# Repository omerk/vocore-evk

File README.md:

# vocore-evk

An evaluation kit for [VoCore](https://www.indiegogo.com/projects/vocore-a-coin-sized-linux-computer-with-wifi), the coin-sized Linux computer with WiFi.

### Design Status

Alpha (untested!)

### License

This work is licensed under a [Creative Commons Attribution-ShareAlike 4.0 International License](http://creativecommons.org/licenses/by-sa/4.0/).

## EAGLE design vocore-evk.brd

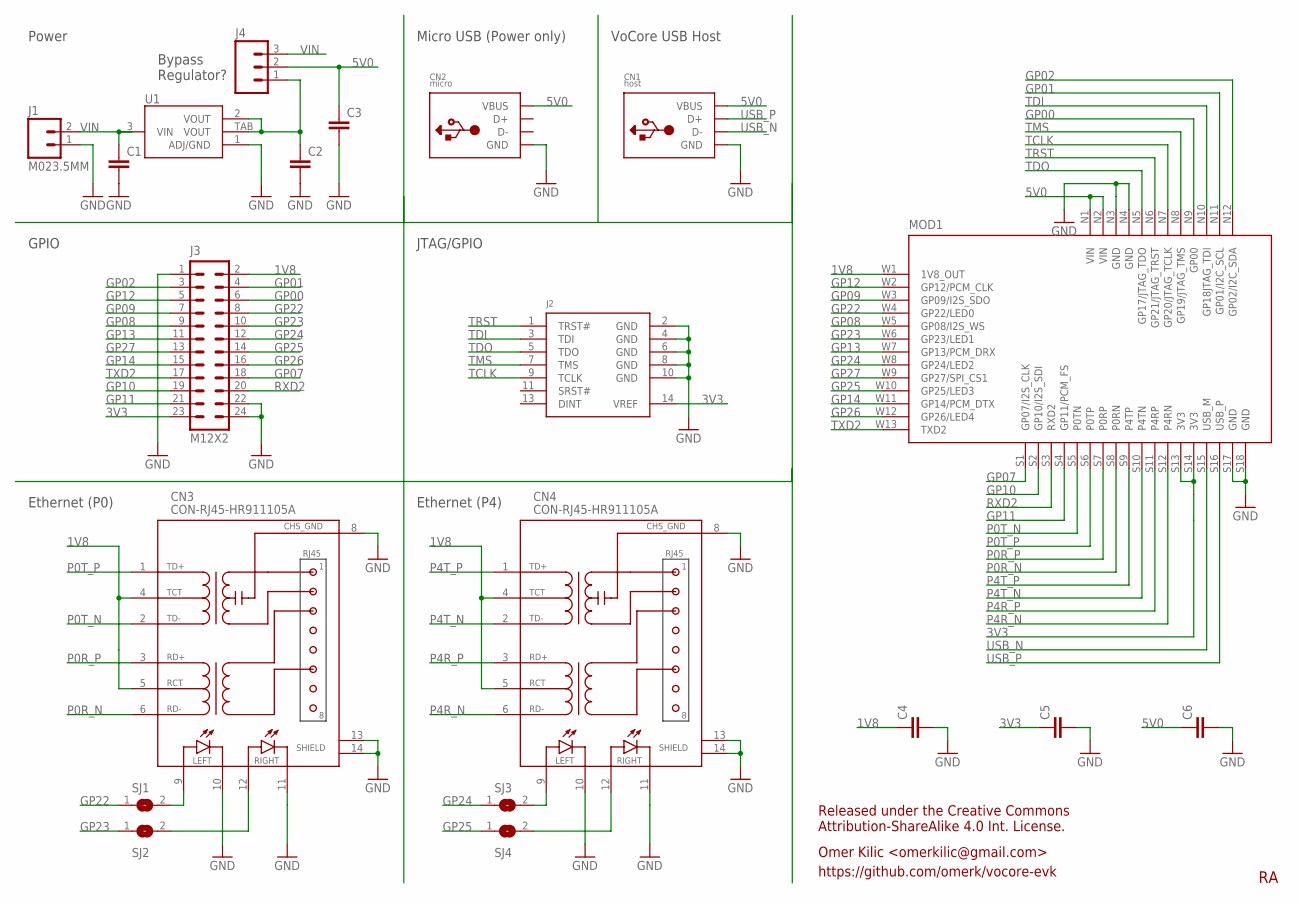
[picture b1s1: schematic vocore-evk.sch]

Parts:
C1, C2, C3, C4, C5, C6: C-EUC0805; C0805
CN1: host; USB-A-FEMALE-TH
CN2: micro; USB-MOLEX-47346-0001
CN3, CN4: CON-RJ45-HR911105A; HR911105A
J1: M023.5MM; SCREWTERMINAL-3.5MM-2
J2: EJTAG_MIPS; M2X7
J3: M12X2; M2X12
J4: M03PTH; 1X03
MOD1: VOCORE_V10A
SJ1, SJ2, SJ3, SJ4: SJ
U1: LDO1117-SOT223; SOT223-3L

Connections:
1V8: C4.1, CN3.4 (TCT), CN3.5 (RCT), CN4.4 (TCT), CN4.5 (RCT), J3.2, MOD1.W1 (1V8_OUT)
3V3: C5.1, J2.14 (VREF), J3.23, MOD1.S13 (3V3), MOD1.S14 (3V3)
5V0: C3.1, C6.1, CN1.VBUS, CN2.VBUS, J4.2, MOD1.N1 (VIN), MOD1.N2 (VIN)
GND: C1.2, C2.2, C3.2, C4.2, C5.2, C6.2, CN1.GND, CN2.GND, CN3.8 (CHS_GND), CN3.10 (LEFT_GRN_LED_K), CN3.11 (RIGHT_YLW_LED_K), CN3.13 (SHIELD), CN3.14 (SHIELD), CN4.8 (CHS_GND), CN4.10 (LEFT_GRN_LED_K), CN4.11 (RIGHT_YLW_LED_K), CN4.13 (SHIELD), CN4.14 (SHIELD), J1.1, J2.2 (GND), J2.4 (GND), J2.6 (GND), J2.8 (GND), J2.10 (GND), J3.1, J3.22, J3.24, MOD1.N3 (GND), MOD1.N4 (GND), MOD1.S17 (GND), MOD1.S18 (GND), U1.1 (ADJ/GND)
GP00: J3.6, MOD1.N9 (GP00)
GP01: J3.4, MOD1.N11 (GP01/I2C_SCL)
GP02: J3.3, MOD1.N12 (GP02/I2C_SDA)
GP07: J3.18, MOD1.S1 (GP07/I2S_CLK)
GP08: J3.9, MOD1.W5 (GP08/I2S_WS)
GP09: J3.7, MOD1.W3 (GP09/I2S_SDO)
GP10: J3.19, MOD1.S2 (GP10/I2S_SDI)
GP11: J3.21, MOD1.S4 (GP11/PCM_FS)
GP12: J3.5, MOD1.W2 (GP12/PCM_CLK)
GP13: J3.11, MOD1.W7 (GP13/PCM_DRX)
GP14: J3.15, MOD1.W11 (GP14/PCM_DTX)
GP22: J3.8, MOD1.W4 (GP22/LED0), SJ1.1
GP23: J3.10, MOD1.W6 (GP23/LED1), SJ2.1
GP24: J3.12, MOD1.W8 (GP24/LED2), SJ3.1
GP25: J3.14, MOD1.W10 (GP25/LED3), SJ4.1
GP26: J3.16, MOD1.W12 (GP26/LED4)
GP27: J3.13, MOD1.W9 (GP27/SPI_CS1)
LED1: CN3.12 (RIGHT_YLW_LED_A), SJ2.2
unnamed: CN3.9 (LEFT_GRN_LED_A), SJ1.2
unnamed: CN4.9 (LEFT_GRN_LED_A), SJ3.2
unnamed: CN4.12 (RIGHT_YLW_LED_A), SJ4.2
P0R_N: CN3.6 (RD-), MOD1.S8 (P0RN)
P0R_P: CN3.3 (RD+), MOD1.S7 (P0RP)
P0T_N: CN3.2 (TD-), MOD1.S5 (P0TN)
P0T_P: CN3.1 (TD+), MOD1.S6 (P0TP)
P4R_N: CN4.6 (RD-), MOD1.S12 (P4RN)
P4R_P: CN4.3 (RD+), MOD1.S11 (P4RP)
P4T_N: CN4.2 (TD-), MOD1.S10 (P4TN)
P4T_P: CN4.1 (TD+), MOD1.S9 (P4TP)
RXD2: J3.20, MOD1.S3 (RXD2)
TCLK: J2.9 (TCLK), MOD1.N7 (GP20/JTAG_TCLK)
TDI: J2.3 (TDI), MOD1.N10 (GP18JTAG_TDI)
TDO: J2.5 (TDO), MOD1.N5 (GP17/JTAG_TDO)
TMS: J2.7 (TMS), MOD1.N8 (GP19/JTAG_TMS)
TRST: J2.1 (TRST#), MOD1.N6 (GP21/JTAG_TRST)
TXD2: J3.17, MOD1.W13 (TXD2)
USB_N: CN1.D-, MOD1.S15 (USB_M)
USB_P: CN1.D+, MOD1.S16 (USB_P)
VIN: C1.1, J1.2, J4.3, U1.3 (VIN)
VREG: C2.1, J4.1, U1.2 (VOUT), U1.TAB (VOUT)

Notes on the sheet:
Micro USB (Power only)
VoCore USB Host
Power
GPIO
JTAG/GPIO
Ethernet (P0)
Ethernet (P4)
Bypass Regulator?
https://github.com/omerk/vocore-evk
Released under the Creative Commons Attribution-ShareAlike 4.0 Int. License.
Omer Kilic <omerkilic@gmail.com>

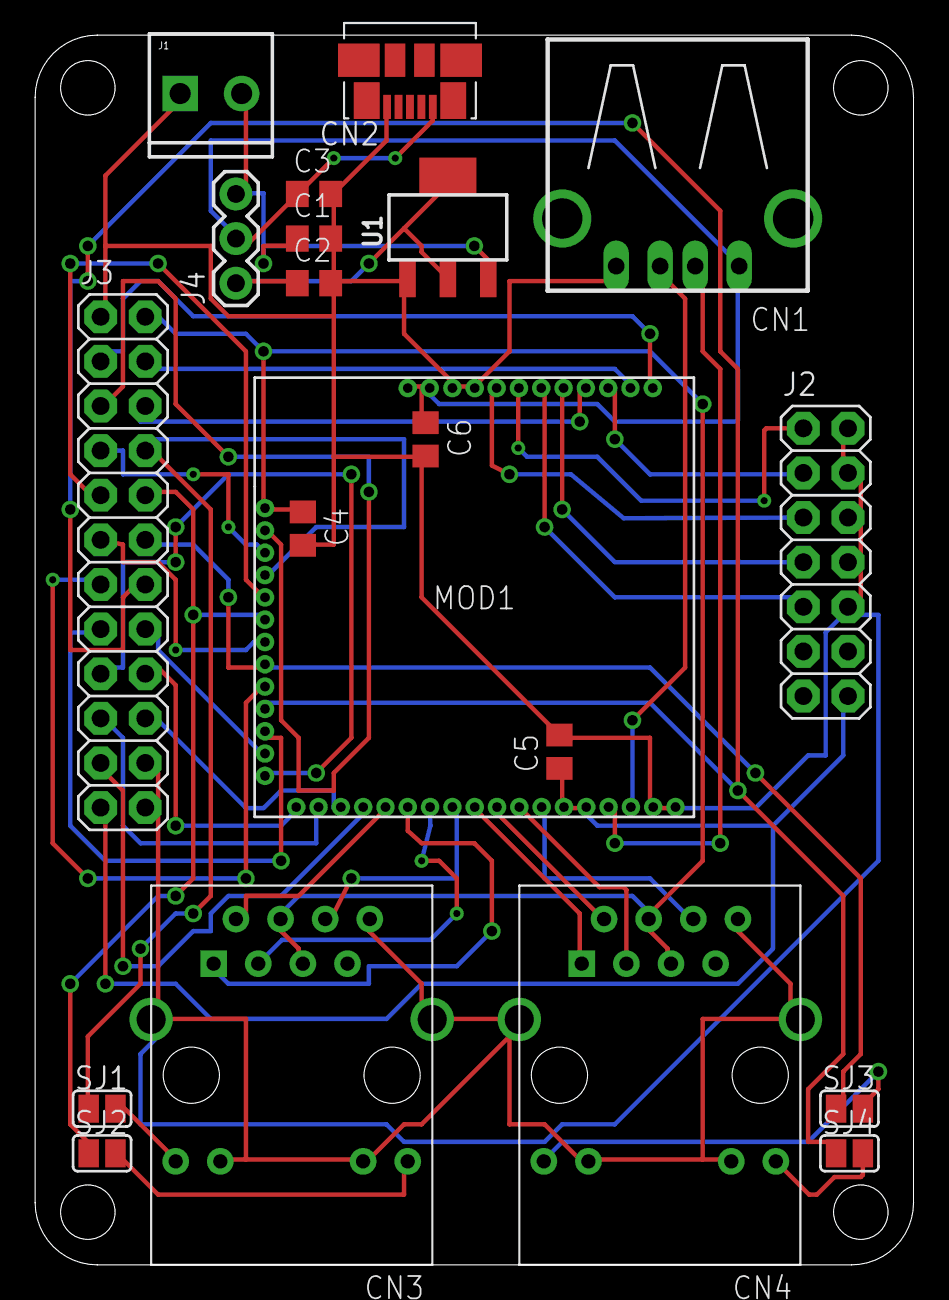
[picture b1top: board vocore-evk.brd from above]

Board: 2 copper layers, 50.0 x 70.0 mm, 20 parts (0 on the bottom side), 44 nets.

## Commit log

2014-06-07 initial commit for the vocore library.
2014-06-07 fix labels for 1V8_OUT and 3V3@2.
2014-06-08 update README, add license.
2014-06-08 add reference material.
2014-06-08 initial commit for the EVK.
2014-06-08 fix license URL.
2014-06-09 Create vocore-eagle5.scr
    Script to create a eagle5 vocore.lbr
2014-06-12 add schematic PDF.
2015-02-04 add vocore-evk inital wireing
2015-02-04 fixed short

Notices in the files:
parts and their libraries:
SparkFun-Connectors: Licensing: Creative Commons ShareAlike 4.0 International - https://creativecommons.org/licenses/by-sa/4.0
